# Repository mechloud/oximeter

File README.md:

# oximeter
Open Source DIY Pulse Oximeter Using Arduino

Instructions:

Plug the device into any usb port (computer, power bank, cellphone charger).

When first turning on the device, an Adafruit logo should appear on the screen for a second or so followed by an SpO2 value screen. 

The value of the first 10 points taken by the device will vary but and after the first 10 points, an average of these points will be taken. From that point on, the device will read a point and take the average of the last 10 points. The average will start to stabilize close to the real value. 

There is a reset button in the middle of the controller if ever you switch users or the average is not stabilizing.

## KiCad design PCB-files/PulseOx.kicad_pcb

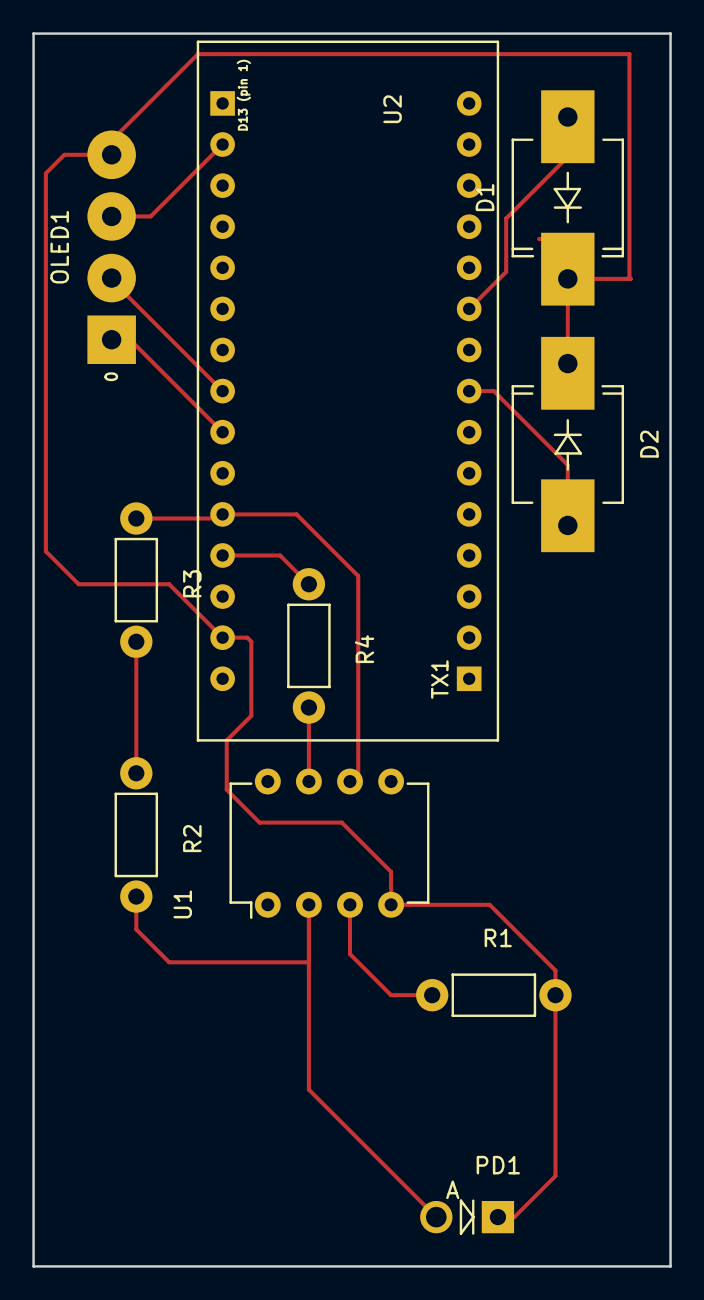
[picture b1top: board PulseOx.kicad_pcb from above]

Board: 2 copper layers, 39.4 x 76.2 mm, 10 parts (0 on the bottom side), 12 nets.

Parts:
D1: Infrared (940nm); SMC-RM10_Universal_Handsoldering
D2: Red (660nm); SMC-RM10_Universal_Handsoldering
OLED1: OLED_Display; SolderWirePad_4xInline_1-2mmDrill
PD1: Photodiode; Diode_DO-41_SOD81_Vertical_AnodeUp
R1: 220; Resistor_Horizontal_RM7mm
R2, R3: 15k; Resistor_Horizontal_RM7mm
R4: 470; Resistor_Horizontal_RM7mm
U1: OP37; DIP-8_W7.62mm
U2: arduino_mini; Arduino_Nano

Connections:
unnamed: D1.1, D2.1, OLED1.4, PD1.1, R1.2, U1.4, U2.14
unnamed: D1.2, U2.21
unnamed: D2.2, U2.23
unnamed: OLED1.1, U2.9
unnamed: OLED1.2, U2.8
unnamed: OLED1.3, U2.2
unnamed: PD1.2, R2.2, U1.2
unnamed: R1.1, U1.3
unnamed: R2.1, R3.2
unnamed: R3.1, U1.6, U2.11
unnamed: R4.1, U2.12
unnamed: R4.2, U1.7

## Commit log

2016-03-28 Added files via upload
2016-03-28 Arduino code with current algorithm
2016-03-28 Oximeter Schematic
2016-03-28 Representation of current circuit
2016-03-28 Bill of Materials
2016-03-28 Fritzing file for schematic and representation
2016-03-28 Adafruit OLED display library
2016-03-28 Adafruit GFX library
2016-03-28 Description and Instructions
2016-06-28 move to folder
2016-06-28 Added all files for current KiCad PCB design
2016-09-01 Latest updated code
    Current working code, includes a lot of 'test' code in comments that still needs editing. Uses running average, median still in the works.
2016-09-01 3D printable clamp design added
    Modified from a model found on thingiverse, top edited to have only 2 holes (LEDs) and bottom single hole in dimensions of the new detector (original fits too) Tested with current hardware, dodgy res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
